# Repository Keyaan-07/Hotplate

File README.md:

# Hotplate
An open-source hotplate designed to take power from USB type-C and then be configured and controlled over Wi-Fi. It uses the ESP32-C3 microcontroller, along with 16MB of storage. There are two terminal blocks to connect with the heating element and it's temperature sensor. There is short circuit protection along with accurate current measurement on the power lines. The control frequency is 10KHz for the heating element. The heating element can be mounted on standoffs so as to not heat the surface below it. 

Check out the Project's files on KiCanvas([PCB](https://github.com/Keyaan-07/Hotplate/tree/main/hardware) and [Heating element](https://github.com/Keyaan-07/Hotplate/tree/main/hardware)) and [Onshape](https://cad.onshape.com/documents/19aaa7739f645838b4ad0ae7/w/c026fb920f31f6c5ff4ae7d0/e/9c380aaf866f8abdd3d2d5e3)!

Features:  
- Upto 45W heating
- Wi-Fi Controlled
- Overcurrent protection & shortcircuit protection. 
- accurate current measurement
- Integrated temperature sensor
- Open Source!
- integrated ADC for NTC temperature readings

wiring diagram between two parts:   
  
##### (made by yours truly in paint)

### Why i made this project
I really wanted to build a custom hotplate so that i could make my own PCBs with ease and not struggle!
The heating element is made up of an aluminium PCB so that there is good thermal conductivity.

### Assembly instructions
1. Upload the gerber files from the [production](/hardware/production/) folder to your specific PCB fab. 
2. Order PCBs and a stencil for soldering. 
3. Order all the parts from the links in the [bom.csv](/bom.csv) file. 
4. Get some solder paste and paste it onto the PCB. pick and place all the components. 
5. heat the PCB in an oven/a reflow station. 
6. connect all the THT components
7. flash the firmware via a USB to UART converter. 
8. connect the heating element. You are done!

### Note about firmware
I dont think i will be able to do the firmware unless and until i have the project in hand, because this requires proper PID tuning to just get the temperature right, and also it needs to be adjusted for errors in temperature measurement and power control!

# BOM
|Sr. No.|Designator                                            |Function             |Value                      |Footprint                                     |Quantity|Price         |Amount |Link                                              |
|-------|------------------------------------------------------|---------------------|---------------------------|----------------------------------------------|--------|--------------|-------|--------------------------------------------------|
|1      |PCB+Stencil                                           |PCB+Stencil          |PCB+Stencil                |PCB+Stencil                                   |5+1     |7+3.07        |10.07  |https://jlcpcb.com/                               |
|2      |Aluminium PCB                                         |Heating element      |                           |                                              |5       |0.8           |4      |https://jlcpcb.com/                               |
|2      |C1, C14, C15, C16, C17, C20, C21, C22, C23, C4, C6, C7|capacitors           |100n                       |402                                           |100     |0.0064        |0.64   |https://www.lcsc.com/product-detail/C100072.html  |
|3      |C10, C11, C8, C9                                      |capacitors           |15p                        |402                                           |100     |0.0102        |1.02   |https://www.lcsc.com/product-detail/C326803.html  |
|4      |C12                                                   |capacitors           |1.8p                       |402                                           |100     |0.0081        |0.81   |https://www.lcsc.com/product-detail/C327209.html  |
|5      |C13                                                   |capacitors           |1.2p                       |402                                           |100     |0.0055        |0.55   |https://www.lcsc.com/product-detail/C327292.html  |
|6      |C18, C19, C24                                         |capacitors           |1u                         |402                                           |50      |0.0162        |0.81   |https://www.lcsc.com/product-detail/C52923.html   |
|7      |C2, C25, C26, C27, C3, C5                             |capacitors           |10u                        |805                                           |20      |0.1007        |2.014  |https://www.lcsc.com/product-detail/C15850.html   |
|8      |D1, D2                                                |LED                  |LED                        |402                                           |50      |0.0084        |0.42   |https://www.lcsc.com/product-detail/C25503345.html|
|9      |D3, D4                                                |ESD protection diodes|ESDA5V3L                   |SOT-23-3                                      |5       |0.1017        |0.5085 |https://www.lcsc.com/product-detail/C87911.html   |
|10     |D5                                                    |buck diode           |1N4148W                    |D_SOD-123                                     |50      |0.0084        |0.42   |https://www.lcsc.com/product-detail/C917030.html  |
|11     |J1                                                    |USB connector        |USB_C_Receptacle_USB2.0_16P|USB_C_Receptacle_XKB_U262-16XN-4BVC11         |10      |0.062         |0.62   |https://www.lcsc.com/product-detail/C393939.html  |
|12     |J2, J3                                                |Screw terminals      |Screw_Terminal_01x02       |TerminalBlock_MaiXu_MX126-5.0-02P_1x02_P5.00mm|5       |0.102         |0.51   |https://www.lcsc.com/product-detail/C474881.html  |
|13     |J4                                                    |                     |Conn_01x04_Pin             |PinHeader_1x04_P2.54mm_Vertical               |5       |0.0319        |0.1595 |https://www.lcsc.com/product-detail/C32713270.html|
|14     |L1, L2                                                |                     |4.7u                       |805                                           |5       |0.1004        |0.502  |https://www.lcsc.com/product-detail/C17701166.html|
|15     |L3                                                    |                     |3n                         |402                                           |20      |0.0042        |0.084  |https://www.lcsc.com/product-detail/C142230.html  |
|16     |Q1, Q2, Q3                                            |                     |AON7262E                   |DFN-5-1EP_3x3mm_P0.65mm_AON7262E              |3       |0.65          |1.95   |https://www.lcsc.com/product-detail/C176755.html  |
|17     |R1                                                    |                     |30                         |402                                           |100     |0.0006        |0.06   |https://www.lcsc.com/product-detail/C54920779.html|
|18     |R10, R14, R15, R9                                     |                     |5.1k                       |402                                           |100     |0.0054        |0.54   |https://www.lcsc.com/product-detail/C105872.html  |
|19     |R11                                                   |                     |1k                         |402                                           |100     |0.0041        |0.41   |https://www.lcsc.com/product-detail/C106235.html  |
|20     |R12, R13                                              |                     |100k                       |402                                           |100     |0.0044        |0.44   |https://www.lcsc.com/product-detail/C60491.html   |
|21     |R16, R18, R3, R6, TH1                                 |                     |10k                        |402                                           |100     |0.0038        |0.38   |https://www.lcsc.com/product-detail/C60490.html   |
|22     |R17                                                   |                     |31.6k                      |402                                           |100     |0.0021        |0.21   |https://www.lcsc.com/product-detail/C2998091.html |
|23     |R2                                                    |                     |56k                        |402                                           |100     |0.0018        |0.18   |https://www.lcsc.com/product-detail/C2906875.html |
|24     |R4, R7, R8                                            |                     |100                        |402                                           |100     |0.0044        |0.44   |https://www.lcsc.com/product-detail/C106232.html  |
|25     |R5                                                    |                     |5m                         |805                                           |10      |0.0514        |0.514  |https://www.lcsc.com/product-detail/C22450690.html|
|26     |U1                                                    |                     |ESP32-C3                   |QFN-32-1EP_5x5mm_P0.5mm_EP3.7x3.7mm           |1       |1.85          |1.85   |https://www.lcsc.com/product-detail/C2838500.html |
|27     |U10                                                   |                     |W25Q128JVP                 |WSON-8-1EP_6x5mm_P1.27mm_EP3.4x4.3mm          |1       |3.47          |3.47   |https://www.lcsc.com/product-detail/C190862.html  |
|28     |U2                                                    |                     |TPS56339DDC                |SOT-23-6                                      |1       |0.37          |0.37   |https://www.lcsc.com/product-detail/C2071106.html |
|29     |U3                                                    |                     |AP33772SDKZ-xx-FA02        |QFN-24-1EP_4x4mm_P0.5mm_EP2.7x2.7mm           |1       |2.69          |2.69   |https://www.lcsc.com/product-detail/C5244513.html |
|30     |U4, U6                                                |                     |TXS0101DBV                 |SOT-23-6                                      |2       |0.585         |1.17   |https://www.lcsc.com/product-detail/C132604.html  |
|31     |U5                                                    |                     |TMP100                     |SOT-23-6                                      |1       |1.02          |1.02   |https://www.lcsc.com/product-detail/C31810.html   |
|32     |U7                                                    |                     |ADS1110                    |SOT-23-6                                      |1       |1.5           |1.5    |https://www.lcsc.com/product-detail/C16598.html   |
|33     |U8                                                    |                     |LM2842Y                    |TSOT-23-6                                     |5       |0.2226        |1.113  |https://www.lcsc.com/product-detail/C30170092.html|
|34     |U9                                                    |                     |MCP1416                    |SOT-23-5                                      |1       |0.52          |0.52   |https://www.lcsc.com/product-detail/C83775.html   |
|35     |Y1                                                    |                     |40MHz                      |Crystal_SMD_3225-4Pin_3.2x2.5mm               |5       |0.0681        |0.3405 |https://www.lcsc.com/product-detail/C5261245.html |
|36     |Y2                                                    |                     |32.786KHz                  |Crystal_SMD_3215-2Pin_3.2x1.5mm               |5       |0.19          |0.95   |https://www.lcsc.com/product-detail/C46604081.html|
|       |                                                      |                     |                           |                                              |        |Total         |43.2555|                                                  |
|       |                                                      |                     |                           |                                              |        |Parts shipping|11     |                                                  |
|       |                                                      |                     |                           |                                              |        |JLC shipping  |16.7   |                                                  |
|       |                                                      |                     |                           |                                              |        |total         |70.9555|                                                  |

# License
Licensed under the MIT license.

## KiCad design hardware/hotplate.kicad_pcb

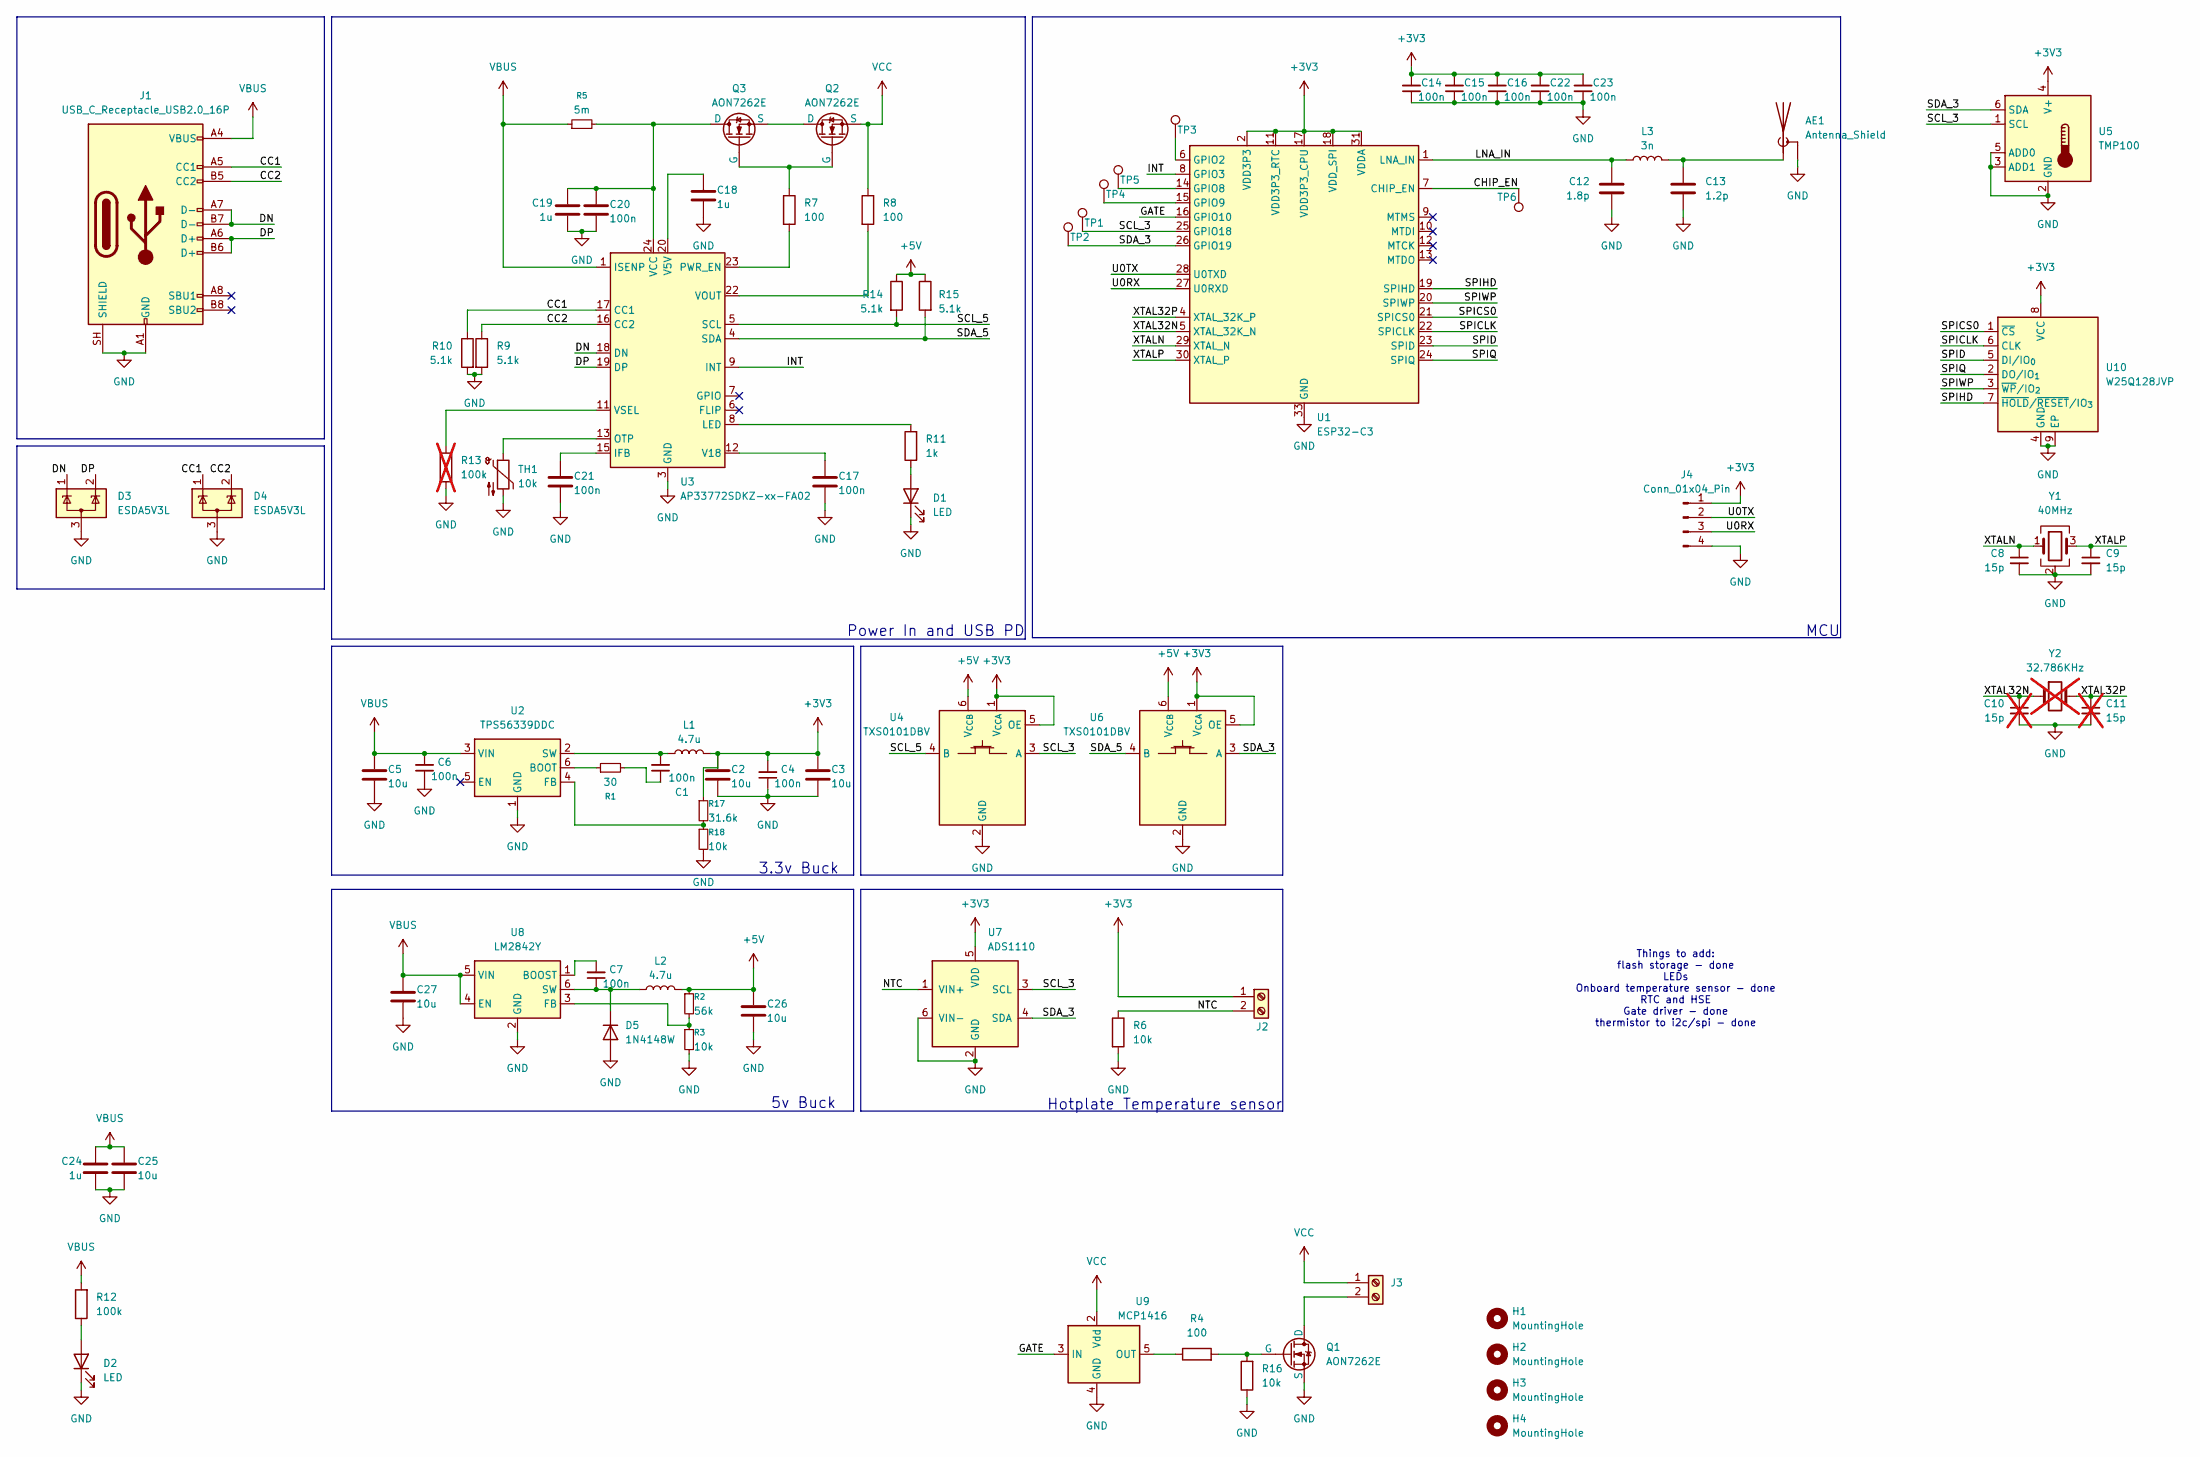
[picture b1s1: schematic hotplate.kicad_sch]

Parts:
AE1: Antenna_Shield; Texas_SWRA117D_2.4GHz_Left
C1, C4, C6, C7, C14, C15, C16, C17, C20, C21, C22, C23: 100n; C_0402_1005Metric
C2, C3, C5, C25, C26, C27: 10u; C_0805_2012Metric
C8, C9: 15p; C_0402_1005Metric
C10, C11: 15p; C_0402_1005Metric; not fitted
C12: 1.8p; C_0402_1005Metric
C13: 1.2p; C_0402_1005Metric
C18, C19, C24: 1u; C_0402_1005Metric
D1, D2: LED; LED_0402_1005Metric
D3, D4: ESDA5V3L; SOT-23-3
D5: 1N4148W; D_SOD-123
H1, H2, H3, H4: MountingHole; MountingHole_3.2mm_M3
J1: USB_C_Receptacle_USB2.0_16P; USB_C_Receptacle_XKB_U262-16XN-4BVC11
J2, J3: Screw_Terminal_01x02; TerminalBlock_MaiXu_MX126-5.0-02P_1x02_P5.00mm
J4: Conn_01x04_Pin; PinHeader_1x04_P2.54mm_Vertical
L1, L2: 4.7u; L_0805_2012Metric
L3: 3n; L_0402_1005Metric
Q1, Q2, Q3: AON7262E; DFN-5-1EP_3x3mm_P0.65mm_AON7262E
R1: 30; R_0402_1005Metric
R2: 56k; R_0402_1005Metric
R3, R6, R16, R18: 10k; R_0402_1005Metric
R4, R7, R8: 100; R_0402_1005Metric
R5: 5m; R_0805_2012Metric
R9, R10, R14, R15: 5.1k; R_0402_1005Metric
R11: 1k; R_0402_1005Metric
R12: 100k; R_0402_1005Metric
R13: 100k; R_0402_1005Metric; not fitted
R17: 31.6k; R_0402_1005Metric
TH1: 10k; R_0402_1005Metric
TP1, TP2, TP3, TP4, TP5, TP6: TestPoint; TestPoint_Pad_D1.5mm
U1: ESP32-C3; QFN-32-1EP_5x5mm_P0.5mm_EP3.7x3.7mm
U2: TPS56339DDC; SOT-23-6
U3: AP33772SDKZ-xx-FA02; Texas_RTW_WQFN-24-1EP_4x4mm_P0.5mm_EP2.7x2.7mm
U4, U6: TXS0101DBV; SOT-23-6
U5: TMP100; SOT-23-6
U7: ADS1110; SOT-23-6
U8: LM2842Y; TSOT-23-6
U9: MCP1416; SOT-23-5
U10: W25Q128JVP; WSON-8-1EP_6x5mm_P1.27mm_EP3.4x4.3mm
Y1: 40MHz; Crystal_SMD_3225-4Pin_3.2x2.5mm
Y2: 32.786KHz; Crystal_SMD_3215-2Pin_3.2x1.5mm; not fitted

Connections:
+3V3: C2.1, C3.1, C4.2, C14.2, C15.2, C16.2, C22.2, C23.2, J2.1, J4.1, L1.2, R17.1, U1.2 (VDD3P3), U1.3 (VDD3P3), U1.11 (VDD3P3_RTC), U1.17 (VDD3P3_CPU), U1.18 (VDD_SPI), U1.31 (VDDA), U1.32 (VDDA), U4.1 (V_{CCA}), U4.5 (OE), U5.4 (V+), U6.1 (V_{CCA}), U6.5 (OE), U7.5 (VDD), U10.8 (VCC)
+5V: C26.1, L2.2, R2.1, R14.1, R15.1, U4.6 (V_{CCB}), U6.6 (V_{CCB})
/CC1: D4.1 (K), J1.A5 (CC1), R10.1, U3.17 (CC1)
/CC2: D4.2 (K), J1.B5 (CC2), R9.1, U3.16 (CC2)
/CHIP_EN: TP6.1 (1_1), U1.7 (CHIP_EN)
/DN: D3.1 (K), J1.A7 (D-), J1.B7 (D-), U3.18 (DN)
/DP: D3.2 (K), J1.A6 (D+), J1.B6 (D+), U3.19 (DP)
/GATE: U1.16 (GPIO10), U9.3 (IN)
/INT: U1.8 (GPIO3), U3.9 (INT)
/LNA_IN: C12.1, L3.1, U1.1 (LNA_IN)
/NTC: J2.2, R6.1, U7.1 (VIN+)
/SCL_3: TP1.1 (1_1), U1.25 (GPIO18), U4.3 (A), U5.1 (SCL), U7.3 (SCL)
/SCL_5: R14.2, U3.5 (SCL), U4.4 (B)
/SDA_3: TP2.1 (1_1), U1.26 (GPIO19), U5.6 (SDA), U6.3 (A), U7.4 (SDA)
/SDA_5: R15.2, U3.4 (SDA), U6.4 (B)
/SPICLK: U1.22 (SPICLK), U10.6 (CLK)
/SPICS0: U1.21 (SPICS0), U10.1 (~CS)
/SPID: U1.23 (SPID), U10.5 (DI/IO_{0})
/SPIHD: U1.19 (SPIHD), U10.7 (~HOLD/~RESET/IO_{3})
/SPIQ: U1.24 (SPIQ), U10.2 (DO/IO_{1})
/SPIWP: U1.20 (SPIWP), U10.3 (~WP/IO_{2})
/U0RX: J4.3, U1.27 (U0RXD)
/U0TX: J4.2, U1.28 (U0TXD)
/XTAL32N: C10.1, U1.5 (XTAL_32K_N), Y2.1
/XTAL32P: C11.1, U1.4 (XTAL_32K_P), Y2.2
/XTALN: C8.1, U1.29 (XTAL_N), Y1.1
/XTALP: C9.1, U1.30 (XTAL_P), Y1.3
GND: AE1.2 (Shield), C2.2, C3.2, C4.1, C5.2, C6.1, C8.2, C9.2, C10.2, C11.2, C12.2, C13.2, C14.1, C15.1, C16.1, C17.2, C18.2, C19.2, C20.2, C21.2, C22.1, C23.1, C24.2, C25.2, C26.2, C27.2, D1.1 (K), D2.1 (K), D3.3 (A), D4.3 (A), D5.2 (A), J1.A1 (GND), J1.A12 (GND), J1.B1 (GND), J1.B12 (GND), J1.SH (SHIELD), J4.4, Q1.1 (S), Q1.2 (S), Q1.3 (S), R3.2, R6.2, R9.2, R10.2, R13.2, R16.1, R18.2, TH1.2, U1.33 (GND), U2.1 (GND), U3.3 (GND), U3.25 (GND), U4.2 (GND), U5.2 (GND), U5.3 (ADD1), U5.5 (ADD0), U6.2 (GND), U7.2 (GND), U7.6 (VIN-), U8.2 (GND), U9.4 (GND), U10.4 (GND), U10.9 (EP), Y1.2 (G), Y1.4 (G)
unnamed: AE1.1 (A), C13.1, L3.2
unnamed: C1.1, R1.2
unnamed: D1.2 (A), R11.1
unnamed: D2.2 (A), R12.1
unnamed: C7.1, D5.1 (K), L2.1, U8.6 (SW)
unnamed: J3.2, Q1.5 (D)
unnamed: Q1.4 (G), R4.2, R16.2
unnamed: Q2.5 (D), Q3.1 (S), Q3.2 (S), Q3.3 (S)
unnamed: Q2.4 (G), Q3.4 (G), R7.1
unnamed: C19.1, C20.1, Q3.5 (D), R5.2, U3.24 (VCC)
unnamed: TP3.1 (1_1), U1.6 (GPIO2)
unnamed: TP5.1 (1_1), U1.14 (GPIO8)
unnamed: TP4.1 (1_1), U1.15 (GPIO9)
unnamed: R1.1, U2.6 (BOOT)
unnamed: R17.2, R18.1, U2.4 (FB)
unnamed: C1.2, L1.1, U2.2 (SW)
unnamed: C21.1, U3.15 (IFB)
unnamed: R11.2, U3.8 (LED)
unnamed: TH1.1, U3.13 (OTP)
unnamed: R7.2, U3.23 (PWR_EN)
unnamed: C18.1, U3.20 (V5V)
unnamed: C17.1, U3.12 (V18)
unnamed: R8.2, U3.22 (VOUT)
unnamed: R13.1, U3.11 (VSEL)
unnamed: C7.2, U8.1 (BOOST)
unnamed: R2.2, R3.1, U8.3 (FB)
unnamed: R4.1, U9.5 (OUT)
VBUS: C5.1, C6.2, C24.1, C25.1, C27.1, J1.A4 (VBUS), J1.A9 (VBUS), J1.B4 (VBUS), J1.B9 (VBUS), R5.1, R12.2, U2.3 (VIN), U3.1 (ISENP), U8.4 (EN), U8.5 (VIN)
VCC: J3.1, Q2.1 (S), Q2.2 (S), Q2.3 (S), R8.1, U9.2 (Vdd)

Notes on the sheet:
3.3v Buck
5v Buck
Things to add: flash storage - done LEDs Onboard temperature sensor - done RTC and HSE Gate driver - done thermistor to i2c/spi - done
Power In and USB PD
Hotplate Temperature sensor
MCU

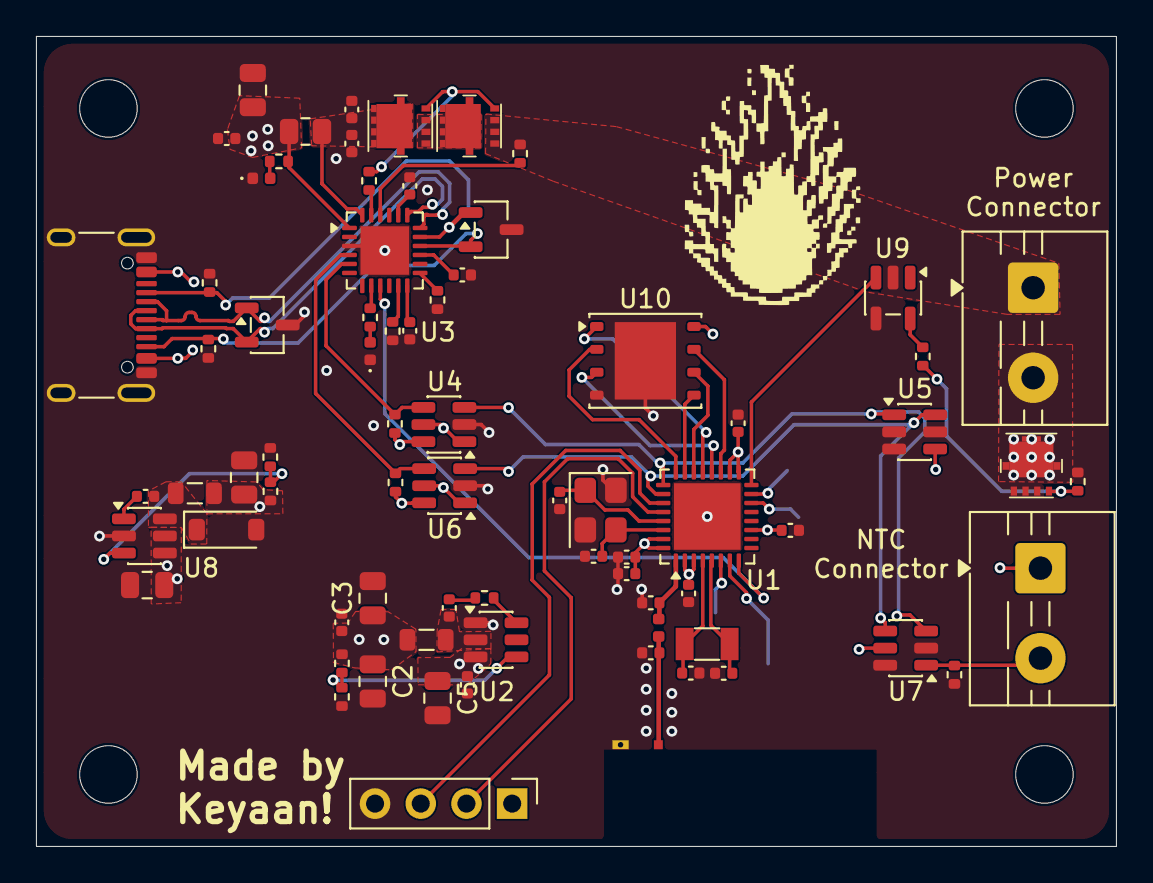
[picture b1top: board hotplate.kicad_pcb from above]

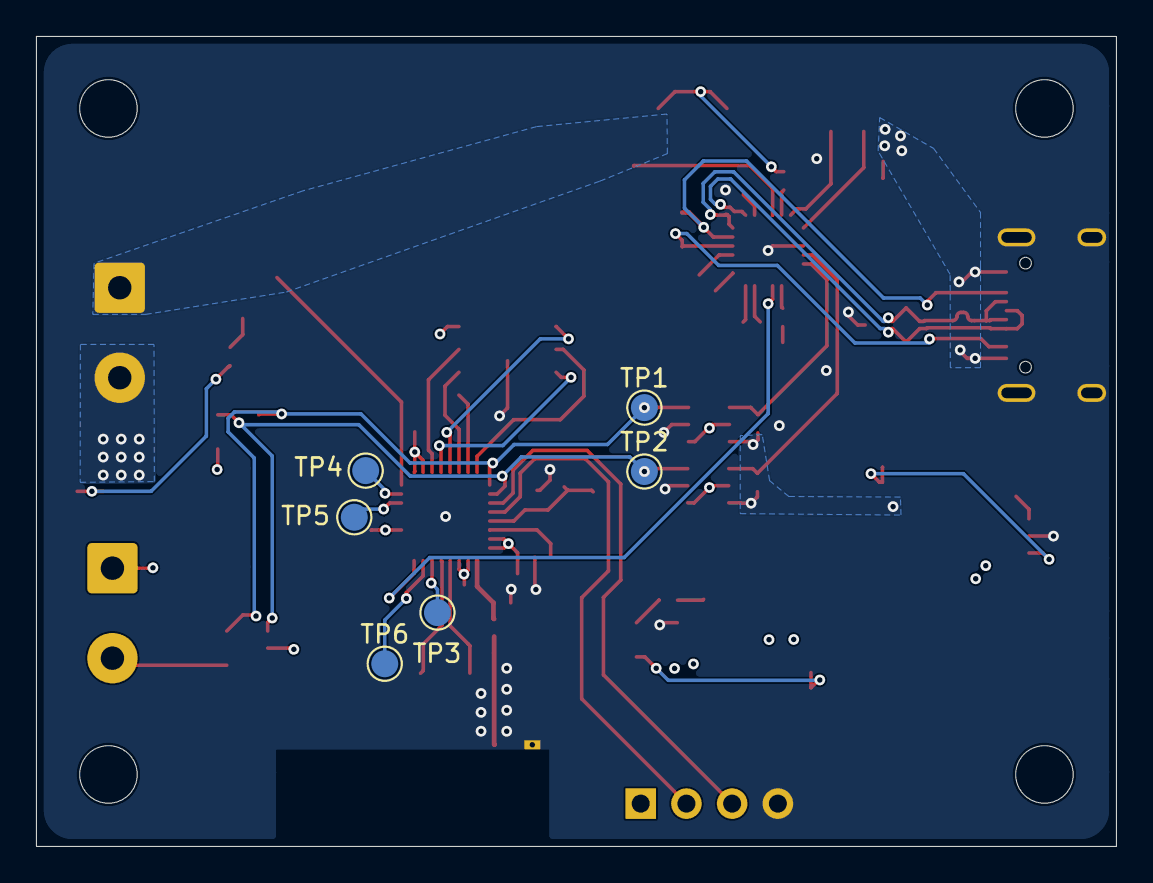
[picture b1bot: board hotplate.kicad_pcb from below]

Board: 4 copper layers, 60.0 x 45.0 mm, 84 parts (6 on the bottom side), 57 nets.

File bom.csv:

Sr. No. ,Designator,Function,Value,Footprint,Quantity,Price,Amount,Link
1,PCB+Stencil,PCB+Stencil,PCB+Stencil,PCB+Stencil,5+1,7+3.07,10.07,https://jlcpcb.com/
2,Aluminium PCB,Heating element,,,5,0.8,4,https://jlcpcb.com/
2,"C1, C14, C15, C16, C17, C20, C21, C22, C23, C4, C6, C7",capacitors,100n,402,100,0.0064,0.64,https://www.lcsc.com/product-detail/C100072.html
3,"C10, C11, C8, C9",capacitors,15p,402,100,0.0102,1.02,https://www.lcsc.com/product-detail/C326803.html
4,C12,capacitors,1.8p,402,100,0.0081,0.81,https://www.lcsc.com/product-detail/C327209.html
5,C13,capacitors,1.2p,402,100,0.0055,0.55,https://www.lcsc.com/product-detail/C327292.html
6,"C18, C19, C24",capacitors,1u,402,50,0.0162,0.81,https://www.lcsc.com/product-detail/C52923.html
7,"C2, C25, C26, C27, C3, C5",capacitors,10u,805,20,0.1007,2.014,https://www.lcsc.com/product-detail/C15850.html
8,"D1, D2",LED,LED,402,50,0.0084,0.42,https://www.lcsc.com/product-detail/C25503345.html
9,"D3, D4",ESD protection diodes,ESDA5V3L,SOT-23-3,5,0.1017,0.5085,https://www.lcsc.com/product-detail/C87911.html
10,D5,buck diode,1N4148W,D_SOD-123,50,0.0084,0.42,https://www.lcsc.com/product-detail/C917030.html
11,J1,USB connector,USB_C_Receptacle_USB2.0_16P,USB_C_Receptacle_XKB_U262-16XN-4BVC11,10,0.062,0.62,https://www.lcsc.com/product-detail/C393939.html
12,"J2, J3",Screw terminals,Screw_Terminal_01x02,TerminalBlock_MaiXu_MX126-5.0-02P_1x02_P5.00mm,5,0.102,0.51,https://www.lcsc.com/product-detail/C474881.html
13,J4,,Conn_01x04_Pin,PinHeader_1x04_P2.54mm_Vertical,5,0.0319,0.1595,https://www.lcsc.com/product-detail/C32713270.html
14,"L1, L2",,4.7u,805,5,0.1004,0.502,https://www.lcsc.com/product-detail/C17701166.html
15,L3,,3n,402,20,0.0042,0.084,https://www.lcsc.com/product-detail/C142230.html
16,"Q1, Q2, Q3",,AON7262E,DFN-5-1EP_3x3mm_P0.65mm_AON7262E,3,0.65,1.95,https://www.lcsc.com/product-detail/C176755.html
17,R1,,30,402,100,0.0006,0.06,https://www.lcsc.com/product-detail/C54920779.html
18,"R10, R14, R15, R9",,5.1k,402,100,0.0054,0.54,https://www.lcsc.com/product-detail/C105872.html
19,R11,,1k,402,100,0.0041,0.41,https://www.lcsc.com/product-detail/C106235.html
20,"R12, R13",,100k,402,100,0.0044,0.44,https://www.lcsc.com/product-detail/C60491.html
21,"R16, R18, R3, R6, TH1",,10k,402,100,0.0038,0.38,https://www.lcsc.com/product-detail/C60490.html
22,R17,,31.6k,402,100,0.0021,0.21,https://www.lcsc.com/product-detail/C2998091.html
23,R2,,56k,402,100,0.0018,0.18,https://www.lcsc.com/product-detail/C2906875.html
24,"R4, R7, R8",,100,402,100,0.0044,0.44,https://www.lcsc.com/product-detail/C106232.html
25,R5,,5m,805,10,0.0514,0.514,https://www.lcsc.com/product-detail/C22450690.html
26,U1,,ESP32-C3,QFN-32-1EP_5x5mm_P0.5mm_EP3.7x3.7mm,1,1.85,1.85,https://www.lcsc.com/product-detail/C2838500.html
27,U10,,W25Q128JVP,WSON-8-1EP_6x5mm_P1.27mm_EP3.4x4.3mm,1,3.47,3.47,https://www.lcsc.com/product-detail/C190862.html
28,U2,,TPS56339DDC,SOT-23-6,1,0.37,0.37,https://www.lcsc.com/product-detail/C2071106.html
29,U3,,AP33772SDKZ-xx-FA02,QFN-24-1EP_4x4mm_P0.5mm_EP2.7x2.7mm,1,2.69,2.69,https://www.lcsc.com/product-detail/C5244513.html
30,"U4, U6",,TXS0101DBV,SOT-23-6,2,0.585,1.17,https://www.lcsc.com/product-detail/C132604.html
31,U5,,TMP100,SOT-23-6,1,1.02,1.02,https://www.lcsc.com/product-detail/C31810.html
32,U7,,ADS1110,SOT-23-6,1,1.5,1.5,https://www.lcsc.com/product-detail/C16598.html
33,U8,,LM2842Y,TSOT-23-6,5,0.2226,1.113,https://www.lcsc.com/product-detail/C30170092.html
34,U9,,MCP1416,SOT-23-5,1,0.52,0.52,https://www.lcsc.com/product-detail/C83775.html
35,Y1,,40MHz,Crystal_SMD_3225-4Pin_3.2x2.5mm,5,0.0681,0.3405,https://www.lcsc.com/product-detail/C5261245.html
36,Y2,,32.786KHz,Crystal_SMD_3215-2Pin_3.2x1.5mm,5,0.19,0.95,https://www.lcsc.com/product-detail/C46604081.html
,,,,,,Total,43.2555,
,,,,,,Parts shipping,11,
,,,,,,JLC shipping,16.7,
,,,,,,total,70.9555,

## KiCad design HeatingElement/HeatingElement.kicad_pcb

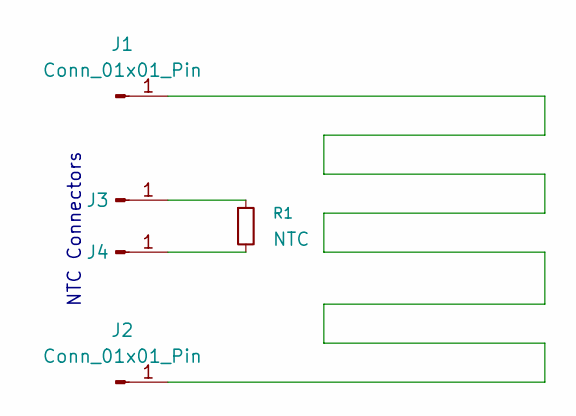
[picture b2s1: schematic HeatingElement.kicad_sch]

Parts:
J1, J2: Conn_01x01_Pin; TestPoint_Pad_4.0x4.0mm
J3, J4: Conn_01x01_Pin; TestPoint_Pad_2.0x2.0mm
R1: NTC; R_0402_1005Metric_Pad0.72x0.64mm_HandSolder

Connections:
unnamed: J1.1 (Pin_1_1), J2.1 (Pin_1_1)
unnamed: J3.1 (Pin_1_1), R1.1
unnamed: J4.1 (Pin_1_1), R1.2

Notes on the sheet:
NTC Connectors

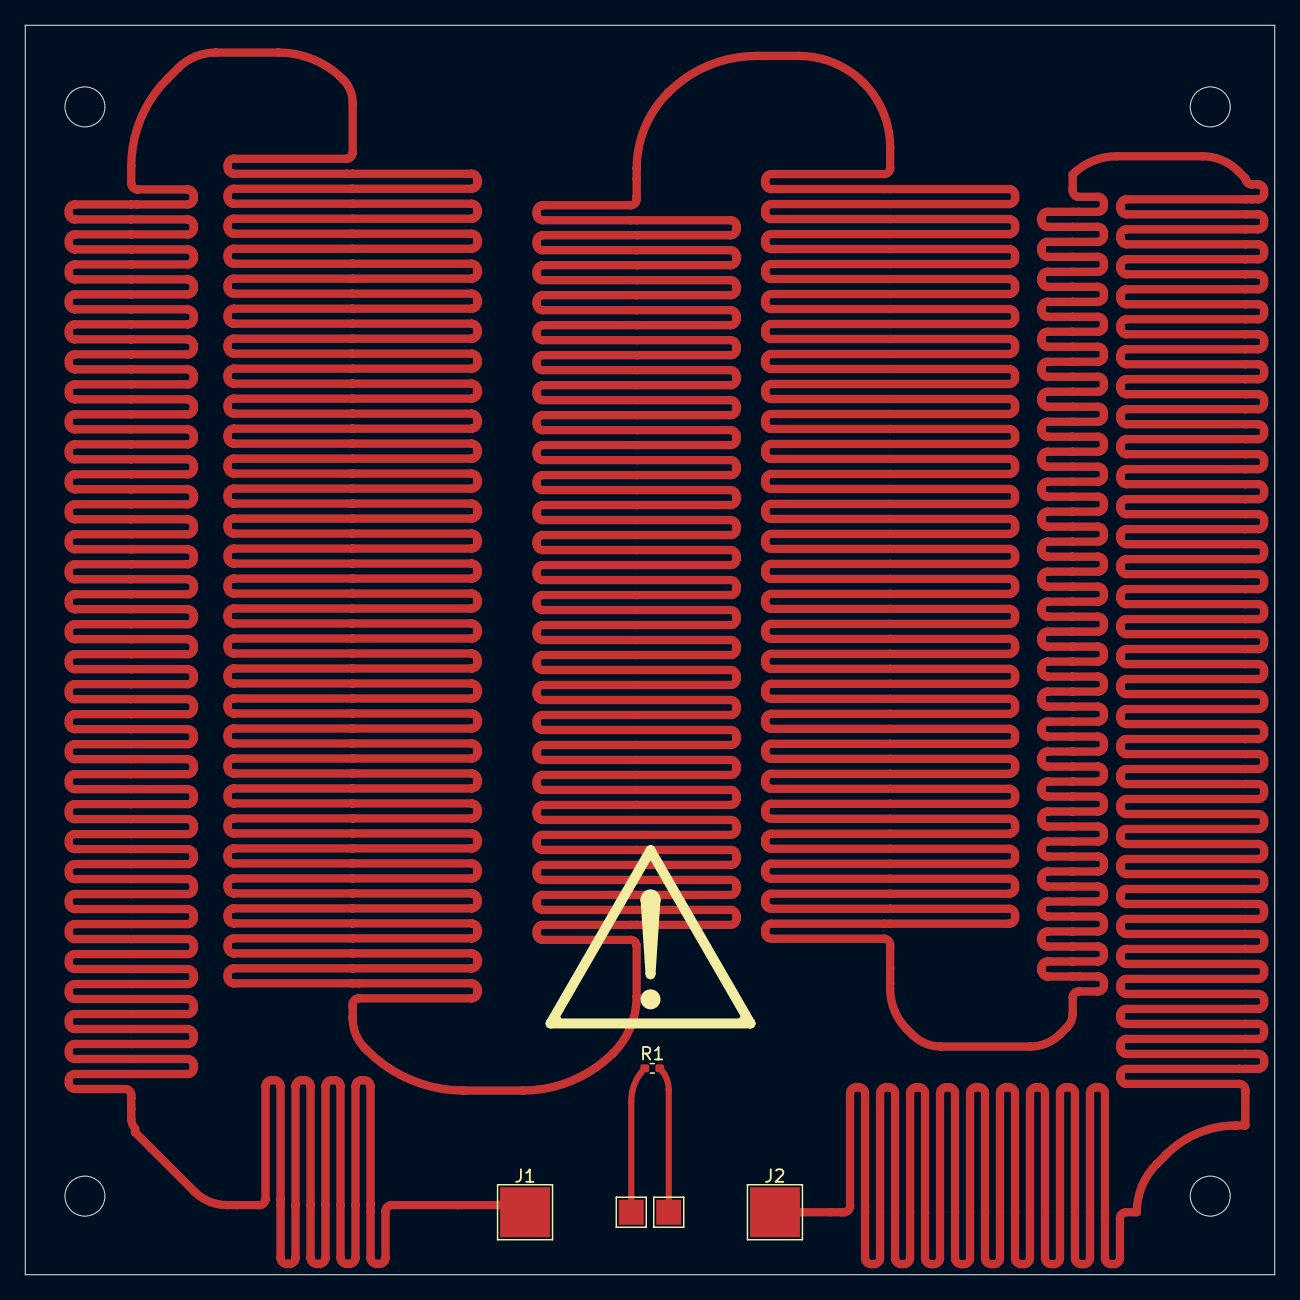
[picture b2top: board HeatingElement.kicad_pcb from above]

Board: 2 copper layers, 100.0 x 100.0 mm, 5 parts (0 on the bottom side), 3 nets.

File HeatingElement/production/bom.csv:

Designator,Footprint,Quantity,Value,LCSC Part #
"J1, J2",TestPoint_Pad_4.0x4.0mm,2,Conn_01x01_Pin,
"J3, J4",TestPoint_Pad_2.0x2.0mm,2,Conn_01x01_Pin,
R1,0402,1,NTC,

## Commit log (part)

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2026-06-15 Hello World
2026-06-15 Hello Readme
2026-06-17 schematic complete(almost)
2026-06-17 Create LICENSE
2026-06-18 hotplate
2026-06-28 hotplate PCB
2026-06-28 AON7262 footprint
2026-06-28 schematic complete
